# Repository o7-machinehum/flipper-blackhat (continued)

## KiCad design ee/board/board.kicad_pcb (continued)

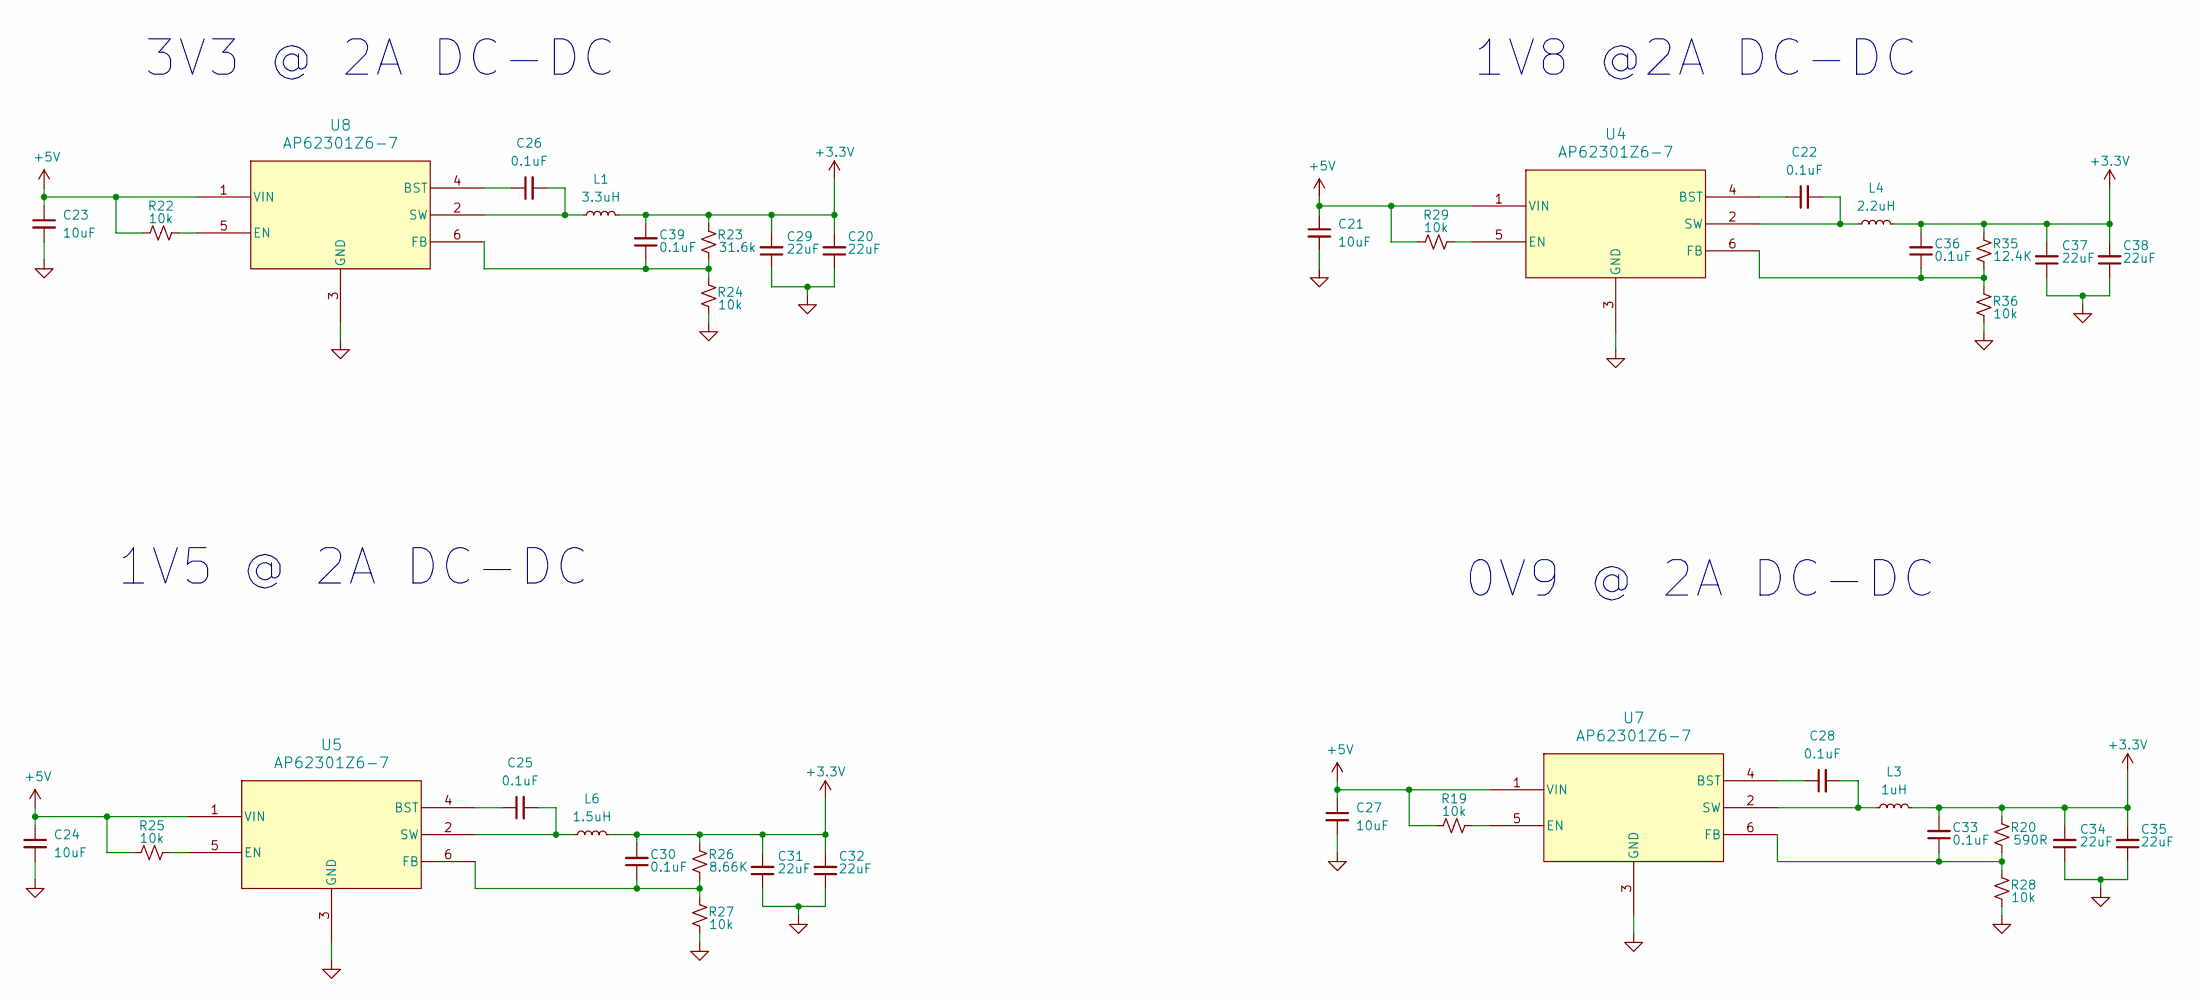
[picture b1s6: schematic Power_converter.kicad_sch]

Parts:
C20, C29, C31, C32, C34, C35, C37, C38: 22uF; C_0603_1608Metric
C21, C23, C24, C27: 10uF; C_0603_1608Metric
C22, C25, C26, C28: 0.1uF; C_0402_1005Metric
C30, C33, C36, C39: 0.1uF; C_0402_1005Metric; MPN MLASE105SB7104KFNA01
L1: 3.3uH; C_0402_1005Metric
L3: 1uH
L4: 2.2uH
L6: 1.5uH
R19, R22, R24, R25, R27, R28, R29, R36: 10k; R_0402_1005Metric
R20: 590R; R_0402_1005Metric
R23: 31.6k; R_0402_1005Metric
R26: 8.66K; R_0402_1005Metric
R35: 12.4K; R_0402_1005Metric
U4, U5, U7, U8: AP62301Z6-7; SOT563-Z6_1_DIO

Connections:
+3.3V: C20.2, C29.2, C30.2, C31.2, C32.2, C33.2, C34.2, C35.2, C36.2, C37.2, C38.2, C39.2, L1.2, L3.2, L4.2, L6.2, R20.2, R23.2, R26.2, R35.2; also elsewhere on the board
+5V: C21.1, C23.1, C24.1, C27.1, R19.1, R22.1, R25.1, R29.1, U4.1 (VIN), U5.1 (VIN), U7.1 (VIN), U8.1 (VIN); also elsewhere on the board
GND: C20.1, C21.2, C23.2, C24.2, C27.2, C29.1, C31.1, C32.1, C34.1, C35.1, C37.1, C38.1, R24.1, R27.1, R28.1, R36.1, U4.3 (GND), U5.3 (GND), U7.3 (GND), U8.3 (GND); also elsewhere on the board
unnamed: C22.1, U4.4 (BST)
unnamed: R29.2, U4.5 (EN)
unnamed: C36.1, R35.1, R36.2, U4.6 (FB)
unnamed: C22.2, L4.1, U4.2 (SW)
unnamed: C25.1, U5.4 (BST)
unnamed: R25.2, U5.5 (EN)
unnamed: C30.1, R26.1, R27.2, U5.6 (FB)
unnamed: C25.2, L6.1, U5.2 (SW)
unnamed: C28.1, U7.4 (BST)
unnamed: R19.2, U7.5 (EN)
unnamed: C33.1, R20.1, R28.2, U7.6 (FB)
unnamed: C28.2, L3.1, U7.2 (SW)
unnamed: C26.1, U8.4 (BST)
unnamed: R22.2, U8.5 (EN)
unnamed: C39.1, R23.1, R24.2, U8.6 (FB)
unnamed: C26.2, L1.1, U8.2 (SW)

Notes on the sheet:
0V9 @ 2A DC-DC
3V3 @ 2A DC-DC
1V5 @ 2A DC-DC
1V8 @2A DC-DC

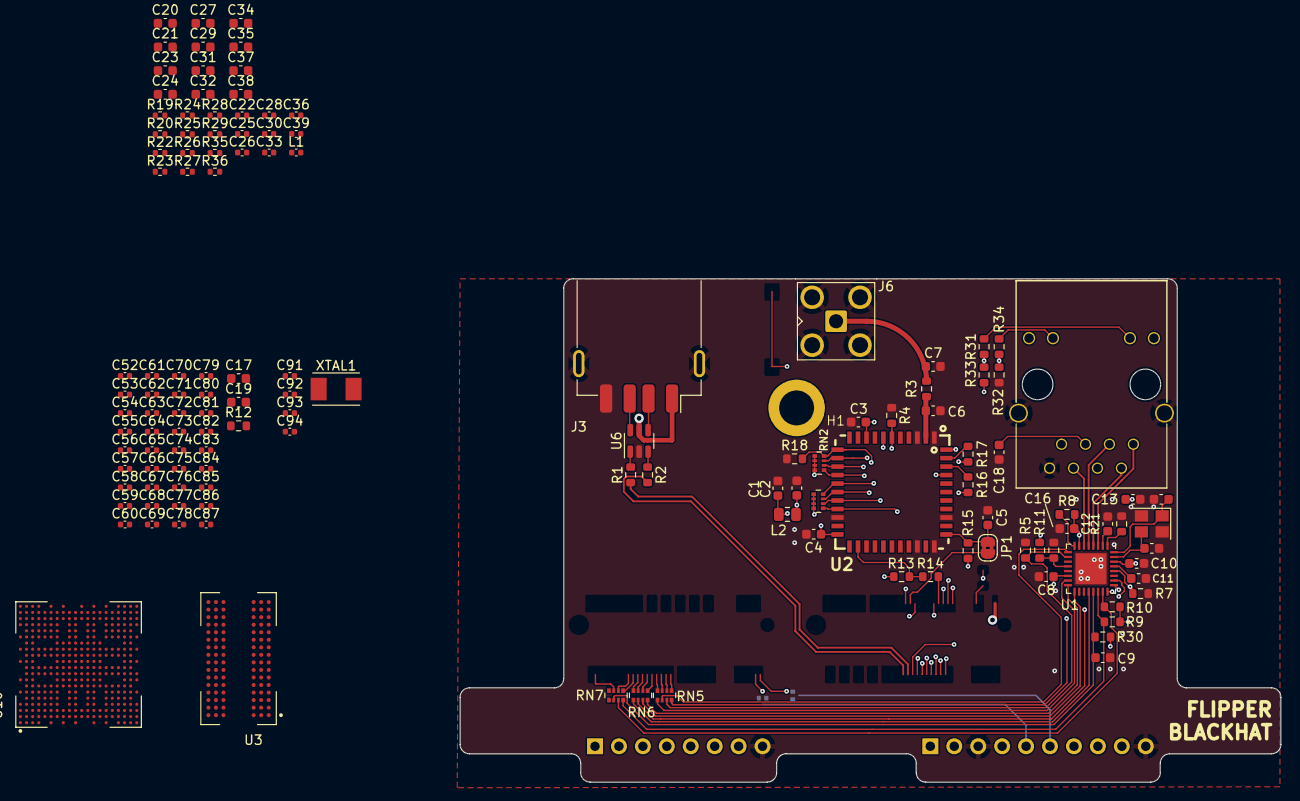
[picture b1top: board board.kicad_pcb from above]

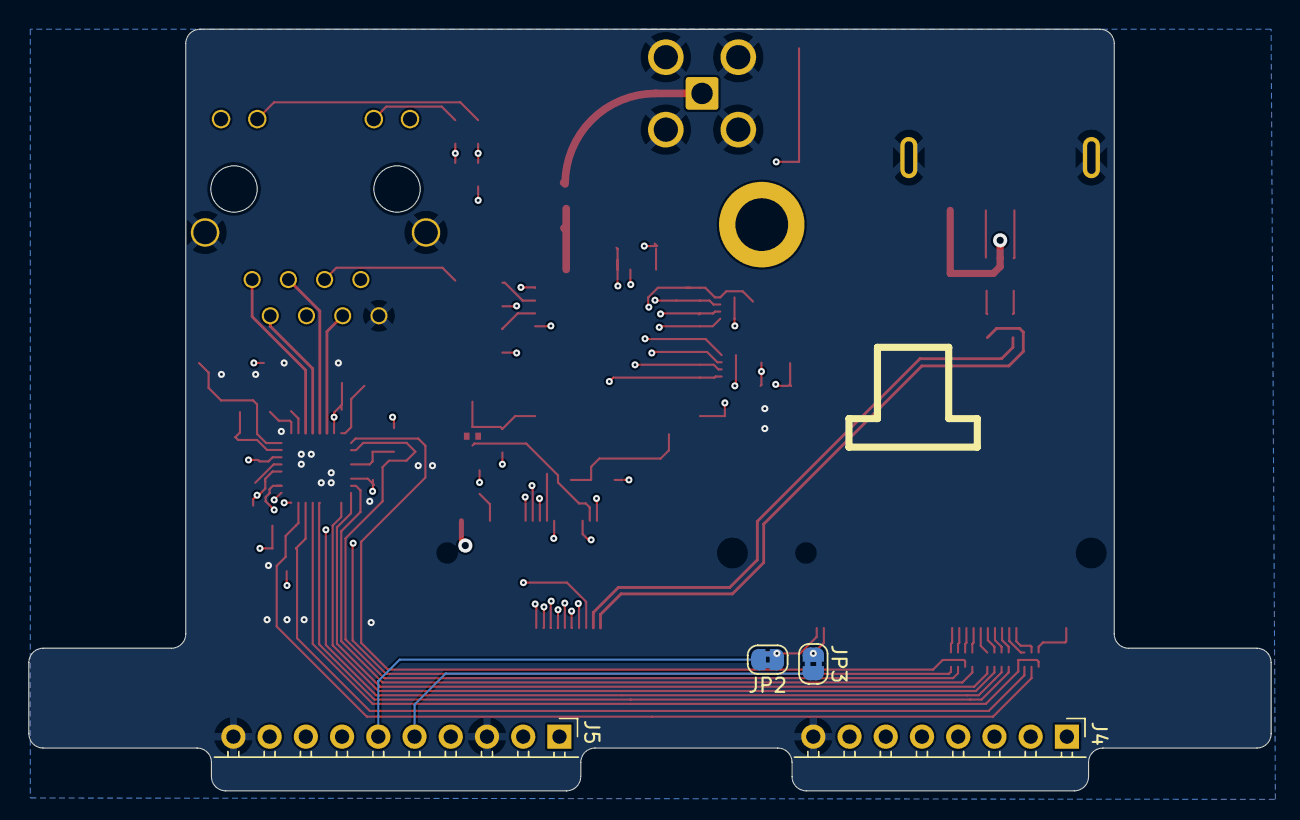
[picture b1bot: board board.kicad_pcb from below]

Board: 4 copper layers, 87.1 x 53.4 mm, 138 parts (4 on the bottom side), 123 nets.

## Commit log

2023-11-09 Initial commit.
2023-11-27 Dropped in the M.2 connectors.
2023-11-29 Added in module
2023-11-29 Added the wifi module
2023-11-29 Added new wifi module
2024-01-04 Schematic mostly finished.
2024-01-04 Moved some of the local library stuff into the submodule.
2024-01-04 Moved everything else from the local library into the submodule.
2024-01-06 Nearly finished routing.
2024-01-09 Finished R1
2024-01-16 Changed inductor side in R0.1 to fit the part number.
2024-03-18 Updated the readme.
2024-03-18 formatting
2024-05-06 Moved to a chip scale
2024-05-10 Added the footprints into the design.
2024-05-10 Leftover stuff
2025-04-06 Moved files over to new folder name
2025-04-16 Images
2025-04-17 R0.1 Released
2025-04-20 R21 actually realeased (reduce pad size to fit soldermask.
2025-07-18 Added legacy schematic
2025-08-05 Added Edgar's mech files
2025-12-17 Added Edgar case files
